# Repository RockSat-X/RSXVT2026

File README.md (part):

# Virginia Tech RockSat-X 2026 Project.

> [!IMPORTANT]
> Quick link to:
> - [Wallops Testing Procedure](#wallops-testing-procedure).
> - [Remove-Before-Flight Procedure](#remove-before-flight-procedure).
>
> Also check out the [RSXVT2026 Wiki](https://github.com/RockSat-X/RSXVT2026/wiki)!

&nbsp;

# Mission Overview.

Our experiment aims to evaluate the use of optical navigation
with Commercial-off-the-Shelf (COTS) products for use in spaceflight applications.
To conduct the experiment,
an autonomous attitude determination and control system (ADCS)
employing an optical navigation system (ONS)
will be designed to control a 1U CubeSat,
codenamed **Commercial Optical Navigation Satellite (CONSat)**.

The 2024 NASA Civil Space Shortfall Ranking lists 9 out of the top 30 shortfalls
as limitations with autonomous deep space navigation.
With recent advancements in computing and ML capabilities,
optical navigation could revolutionize deep space navigation.
Our team aims to address some of the challenges facing the space industry
by designing a cost-effective ADCS that would rely primarily on conditions
only available in deep space.

The CONSat vehicle's Optical Navigation System (ONS) has:
- OpenMV H7+.
- VN-100 IMU / AHRS.

The operating principle of the CONSat will be to:
1. Capture image and isolate target.
2. Perform LoS measurements to estimate attitude.
3. Blend LoS solution with IMU / AHRS solution.
4. Reorient spacecraft to align to target.

The target will be the Earth's horizon as seen at ~190 km apogee.

&nbsp;

# High-Level System Overview.

<p align="center">
<kbd>

<br>
<br>
<em>Deck-plate integrated experiment.</em>
<br>
<br>
</kbd>
</p>&nbsp;

<p align="center">
<kbd>

<br>
<br>
<em>Top-down view of the deck-plate integrated experiment.</em>
<br>
<br>
</kbd>
</p>&nbsp;

<p align="center">
<kbd>

<br>
<br>
<em>Weight of the deck-plate integrated experiment (13.935 pounds / 6.321 kilograms).</em>
<br>
<br>
</kbd>
</p>&nbsp;

<p align="center">
<kbd>

<br>
<br>
<em>Center of gravity of the deck-plate integrated experiment.</em>
<br>
<br>
</kbd>
</p>&nbsp;

<p align="center">
<kbd>

<br>
<br>
<em>The inside of the main electronics box enclosure.</em>
<br>
<br>
</kbd>
</p>&nbsp;

<p align="center">
<kbd>

<br>
<br>
<em>CONSat vehicle.</em>
<br>
<br>
</kbd>
</p>&nbsp;

<p align="center">
<kbd>

<br>
<br>
<em>The inside of the CONSat vehicle.</em>
<br>
<br>
</kbd>
</p>&nbsp;

<p align="center">
<kbd>

<br>
<br>
<em>Labeled CAD model of the experiment.</em>
<br>
<br>
</kbd>
</p>&nbsp;

<p align="center">
<kbd>

<br>
<br>
<em>Functional block diagram of the CONSat experiment.</em>
<br>
<br>
</kbd>
</p>&nbsp;

## Main Camera System.

The experiment has two Main Camera Systems:
one placed before the ejection mechnism
and one next to a Solarboard by the burn-wire mechanism.

<p align="center">
<kbd>

<br>
<br>
<em>Main Camera System demonstration.</em>
<br>
<br>
</kbd>
</p>&nbsp;

The Main Camera System board has a single RGB LED.

| Color          | Description                                                                                          |
| :------------: | ---------------------------------------------------------------------------------------------------- |
| White          | Reformatting uSD card. |
| Magenta        | Initializing uSD card. |
| Blue           | Initializing OV5640 camera module. |
| Toggling green | Recording successfully. |
| Red            | Main Camera System resetting. |

&nbsp;

The Main Camera System creates a binary blob file for each recording.
Use `cli.py parseVideo` to convert the binary blob file into an MP4 video.

&nbsp;

## Debug Board.

The Debug Board has a display to indicate the status of subsystems
from the perspective of the Main Flight Computer.
When the experiment is powered on via GSE-1,
the Debug Board will initialize and play the Nokia buzzer tune.
The display will also periodically invert color;
this is just to indicate that the Debug Board MCU is still running.

<p align="center">
<kbd>

<br>
<br>
<em>Debug board demonstration.</em>
<br>
<br>
</kbd>
</p>&nbsp;

The Debug Board displays the following information.

| Field     | Description                                                                                          |
| :-------: | ---------------------------------------------------------------------------------------------------- |
| `DB-T`    | Time elapsed since the debug board was powered on.                                                   |
| `MFC-T`   | Time elapsed since the Main Flight Compiuter was powered on.                                         |
| `SCB-A`   | Voltage of SB-SCA.                                                                |
| `SCB-B`   | Voltage of HP-SCA.                                                                |
| `te1`     | Whether or not Main Flight Computer is detecting TE-1.                                               |
| `vehicle` | Whether or not Main Flight Computer is communicating with the Vehicle Flight Computer through the vehicle interface. |
| `esp32`   | Whether or not Main Flight Computer is receiving ESP-NOW data packets.                               |
| `lora`    | Whether or not Main Flight Computer is receiving LoRa data packets.                                  |
| `logger`  | Whether or not Main Flight Computer is saving data to its uSD card.                                  |

If the Debug Board has not received the first debug packet from the Main Flight Computer yet,
then the field values will either be `???` or `nan` to indicate this.

> [!IMPORTANT]
> A known issue with the Debug Board's display is that it is not resettable.
> That is, if the Debug Board MCU has a communication issue with the display driver,
> there's a small possibility that the display ends up in a corrupted state.
> This may appear as the screen being darker, the resolution looking off,
> or is completely blank.
> The MCU has no way to fix this,
> but power-cycling will resolve this rare issue if it ever happens.

&nbsp;

The debug board has four RGB LEDs.

| Label     | Position     | Description                                                                                          |
| :-------: | :----------: | ---------------------------------------------------------------------------------------------------- |
| `A`       | Top Right    | Flashes colors when the buzzer is being driven; this is just an extra indicator that's useful for when the buzzer is mute. |
| `B`       | Top Left     | White when the Main Flight Computer hasn't sent the first debug packet to the Debug Board yet; red when there's a bad status to be aware of such as the Main Flight Computer not having received RF data in a while. |
| `C`       | Bottom Right | Toggles red when the Main Flight Computer hasn't sent a debug packet in a while; toggles green when a debug packet has been received. |
| `D`       | Bottom Left  | White when the uSD card is being formatted; magenta when the Debug Board is failing to initialize the uSD card; toggles green periodically when data is successfully being logged to the uSD card. |

> [!IMPORTANT]
> If the Debug Board encounters an irrecoverable error,
> it'll panic and indicate this by flashing all LEDs red.
> The Debug Board should eventually reset itself and continue on as normal.

&nbsp;

The debug board plays the following buzzer tunes.

| Tune                                        | Description                                                                    |
| :---------:                                 | ------------------------------------------------------------------------------ |
| [Nokia      ](./misc/media/nokia.wav      ) | Debug Board is initializing (e.g. just powered on from GSE-1). |
| [Hazard     ](./misc/media/hazard.wav     ) | Debug Board hasn't received a debug packet from the Main Flight Computer in a while. |
| [Up and Down](./misc/media/up_and_down.wav) | `te1` is active (i.e. burn-wire is going). |
| [Deep Beep  ](./misc/media/deep_beep.wav  ) | Main Flight Computer is reporting a bad status (e.g. haven't received RF data in a while) |
| [Tetris     ](./misc/media/tetris.wave    ) | The Debug Board's uSD card is being reformatted. |

To mute the buzzer, leave the header above the buzzer open.
To enable the buzzer, have a jumper shorting two adjacent pins;
which pins are shorted determines the volume of the buzzer.

&nbsp;

The uSD card is optional to the operation of the Debug Board.
The Debug Board uses LED D to indicate that it's successfully saving log data.

<p align="center">
<kbd>

<br>
<br>
<em>
To load a uSD card, lift the connector lid up,
<br>
place the uSD card,
and slide the lid down to secure it.
</em>
<br>
<br>
</kbd>
</p>&nbsp;

<p align="center">
<kbd>

<br>
<br>
<em>
The Debug Board creates an ASCII text file with <br>
the same information displayed on its screen.
</em>
<br>
<br>
</kbd>
</p>&nbsp;

## Vehicle Flight Computer.

The following table details the corresponding buzzer tune and RGB LED behavior for when a Vehicle Flight Computer diagnostic is reported.

| Severity | Tune                                              | RGB LED                 | Description                                                                                          |
|:-:| :-----------------------------------------------: | :-----------------: | ---------------------------------------------------------------------------------------------------- |
| :bangbang:         | [Ambulance  ](./misc/media/ambulance.wav      )   | Fast toggling red   | TMC2209 stepper motor drivers are failing initialization. This could be due to bad ribbon cable connection, dead batteries, inhibited batteries, or something else. |
| :warning:          | [Heartbeat  ](./misc/media/heartbeat.wav      )   | Slow toggling red   | Vehicle Flight Computer has saturated a motor's RPM velocity. |
| :warning:          | [Tetris     ](./misc/media/tetris.wav         )   | Slow toggling white | Vehicle Flight Computer is reformatting the uSD card. |
| :warning:          | [Mario      ](./misc/media/mario.wav          )   | Fast toggling white | Resetting the Vehicle ESP32 due to an issue with it. |
| :warning:          | [Three Tone ](./misc/media/three_tone.wav     )   | Fast toggling white | Resetting the Vehicle OpenMV due to an issue with it. |
| :bangbang:         | [Hazard     ](./misc/media/hazard.wav         )   | Fast toggling blue  | Communication issue with VN-100. |
| :white_check_mark: | [Nokia      ](./misc/media/nokia.wav          )   | Slow toggling white | Vehicle Flight Computer detecting that the vehicle has been redocked. |
| :white_check_mark: | [Birthday   ](./misc/media/birthday.wav       )   | Slow toggling white | Vehicle Flight Computer detecting that the vehicle has been ejected. |
| :warning:          | [Heavy Beep ](./misc/media/heavy_beep.wav     )   | Toggling magenta    | Initialization issue with uSD card. This is okay if no uSD card is loaded. |
| :white_check_mark: | [Burp       ](./misc/media/burp.wav           )   | Blue blink          | VN-100 communication okay. |
| :white_check_mark: | [Chirp      ](./misc/media/chirp.wav          )   | Green blink         | uSD card logging okay. |
| :white_check_mark: | [Waking Up  ](./misc/media/waking_up.wav      )   | None                | Vehicle Flight Computer initializing (i.e. on activation of GSE-1); vehicle batteries are enabled at end of buzzer tune. |
| :white_check_mark: | [Star Wars  ](./misc/media/starwars.wav       )   | None                | Vehicle Flight Computer performing a dock shutdown (i.e. about to turn vehicle batteries off and resetting). |

| Severity            | Description                                                                                          |
| :-----------------: | ---------------------------------------------------------------------------------------------------- |
| :bangbang:  | Something is likely very problematic and should be addressed as soon as possible. |
| :warning:  | A non-fatal or recoverable issue. |
| :white_check_mark:  | Positive or expected indicator of a working system. |

The three pin header on the Vehicle Flight Computer can be left open to mute the buzzer,
otherwise short a pair of adjacent pins to determine the volume of the buzzer.

&nbsp;

The Vehicle Flight Computer board also has an optional uSD card slot for log data.

<p align="center">
<kbd>

<br>
<br>
<em>
The Vehicle Flight Computer creates an ASCII text file with information <br>
like VN-100 IMU data, CVT results, current motor velocities, and so on.
</em>
<br>
<br>
</kbd>
</p>&nbsp;

&nbsp;

## OpenMV H7+.

The OpenMV H7+ has a single RGB LED.

| RGB LED             | Description                                                                                          |
| :-----------------: | ---------------------------------------------------------------------------------------------------- |
| Flashing blue       | The CVT algorithm hasn't detected the horizon yet. |
| Flashing green      | The CVT algorithm has found the horizon. |

Each toggle of the RGB LED represents an entire image being captured, processed, and transmitted to the Vehicle Flight Computer.
Because JPEG image compression is used,
if the OpenMV H7+'s camera lens is covered (e.g. by a finger),
the blinking of the RGB LED will be much faster.

If the OpenMV H7+'s RGB LED is not blinking, then it's very likely the program is not running,
but the Vehicle Flight Computer should reset the OpenMV H7+ eventually after a time-out period.

No other colors or behavior should be expected from the RGB LED or the OpenMV H7+ module as a whole.

&nbsp;

## Vehicle Power Distribution System.

The Vehicle Power Distribution System has LED indicators to be aware of.

| LED                 | Description                                                                                          |
| :-----------------: | ---------------------------------------------------------------------------------------------------- |
| Bright white        | Vehicle interface providing power to the vehicle, thus this LED should be active if and only if the vehicle is docked and GSE-1 is active. |
| Yellow              | Vehicle Flight Computer has enabled on-board battery power. The LED should be off when the Vehicle Flight Computer is initializing but should eventually turn on, unless the vehicle battery inhibit is in place, to which this LED will never turn on. |

The Vehicle Power Distribution System has three jumpers to be aware of.

<p align="center">
<kbd>

<br>
<br>
<em>
First jumper on the left denoted with "M" as in "Motor Inhibit". <br>
Second jumper in the middle denoted with "B" as in "Battery Inhibit". <br>
Third jumper on the right denoted with "P" as in "Power". <br>
Note that the third "Power" jumper should only have its <br>
first left pin and the second right pin is broken off.
</em>
<br>
<br>
</kbd>
</p>&nbsp;

| Jumper              | Activation | Description |
| :-----------------: | - | - |
| "M"                 | Use a shorting 2-pin jumper with pull tab. | Disable the control of the stepper motors. Vehicle Flight Computer can still initialize and operate, but reaction wheels will not spin. This is used to conserve battery charge, if needed. |
| "B"                 | Use a shorting 2-pin jumper with pull tab. | Disable the usage of the vehicle batteries. Vehicle Flight Computer can still initialize and operate via external power through the vehicle interface (i.e. GSE-1), but will immediately unpower upon being undocked. This can also be used to turn off the vehicle manually. |
| "P"                 | Use jumper wire to connect the pin to one of the vehicle batteries' positive terminal and wait several seconds. | Forces the usage of vehicle battery power, thus the Vehicle Flight Computer will initialize. This is to turn the vehicle on without relying on external power. |

> [!TIP]
> A quick way to turn off the vehicle is by using an Allen key to short the middle "B" jumper.

&nbsp;

# RF Verification.

During sequence testing and particularly GPS Roll-Out,
it's critical to verify that RF systems are working as intended
and to communicate this to NASA.

The easiest way to do this is to use the [Debug Board](#debug-board).
The screen will indicate if the Main Flight Computer is receiving RF data from the ESP32 and/or LoRa.
If the Debug Board is loaded with a uSD card,
the RF status will also be logged over time.

A more robust way to verify RF is to use the TinySA Spectrum Analyzer.
There are two particular frequency bands of interest.
| Link  | Center         | Bandwidth      | Start          | End            |
| :---: | :------------: | :------------: | :------------: | :------------: |
| ESP32 | 2.472 GHz      | 20 MHz         | 2.462 GHz      | 2.482 GHz      |
| LoRa  | 920 MHz        | 125 kHz        | 919.9375 MHz   | 920.0625 MHz   |

Configure the spectrum analyzer to observe these frequencies.

<p align="center">
</kbd>
<kbd>

<br>
<br>
<em>
Spectrum analyzer demonstration.
</em>
<br>
<br>
</kbd>
</p>&nbsp;

You should see a reading similar the following figures:

<p align="center">
<kbd>

<br>
<br>
<em>
Spectrum analyzer measurement for the ESP32 link.
</em>
<br>
<br>
</p>
<p align="center">
</kbd>
<kbd>

<br>
<br>
<em>
Spectrum analyzer measurement for the LoRa link.
</em>
<br>
<br>
</kbd>
</p>&nbsp;

> [!IMPORTANT]
> The measurements shown in the figures were taken with an RBW value of 200 Hz;
> this makes the measurement more accurate but at the cost of being extremely slow.
> It's probably more productive to use an auto RBW value so measurements can be done quickly.
> Just as long there is an expected peak within frequency bands, all is good.

The RF verification process and expectations should be roughly as follows:

1. Before the experiment is powered on via GSE-1, no RF transmission is detected within the frequency bands.

2. Shortly after the experiment is powered on via GSE-1,
ESP32 and LoRa transmission can be seen within the frequency bands.

3. RF transmission is sustained for at least the duration of a full mission;
if applicable, the RF transmission should still be sustained even if the vehicle has ejected or becomes undocked.

4. RF transmission is sustained even when main has powered off (i.e. GSE-1 deactived)
as the vehicle will continue transmitting via battery power.

5. RF transmission is no longer detected once the vehicle has powered off
(either by using the vehicle battery inhibit or through a docked reset).

&nbsp;

# Wallops Testing Procedure.

The following table summarizes the primary configurations needed to be set for tests done at Wallops.

| Expected Date                           | Test                         | Allow Ejection?    | Enable TE-1?       | Enable Main GSE-1? | Enable Vehicle GSE-1? |
| :-------------------------------------: | :--------------------------: | :-:                | :-:                | :-:                | :-:                   |
| May 17th, 2026; Sunday                  | Pre-Flight Seq.              | :white_check_mark: | :white_check_mark: | :white_check_mark: | :white_check_mark:    |
| May 18th-19th, 2026; Monday-Tuesday     | Pre-Vibe All-Fire Seq.       | :white_check_mark: | :white_check_mark: | :white_check_mark: | :white_check_mark:    |
| May 18th-19th, 2026; Monday-Tuesday     | Pre-Vibe No-Fire Seq.        | :x:                | :x:                | :white_check_mark: | :white_check_mark:    |
| May 19th, 2026; Tuesday                 | Pre-Vibe Back Up Seq.        | :x:                | :x:                | :white_check_mark: | :white_check_mark:    |
| May 20th-21st, 2026; Wednesday-Thursday | Vibration Testing            | :white_check_mark: | :white_check_mark: | :white_check_mark: | :white_check_mark:    |
| May 22nd, 2026; Friday                  | Post-Vibe All-Fire Seq.      | :white_check_mark: | :white_check_mark: | :white_check_mark: | :white_check_mark:    |
| May 22nd, 2026; Friday                  | Post-Vibe No-Fire Seq.       | :x:                | :x:                | :white_check_mark: | :white_check_mark:    |
| May 22nd, 2026; Friday                  | Post-Vibe Back Up Seq.       | :x:                | :x:                | :white_check_mark: | :white_check_mark:    |
| May 22nd, 2026; Friday                  | GPS Roll-Out                 | :x:                | :x:                | :white_check_mark: | :white_check_mark:    |
| June 19th, 2026; Friday                 | Final All-Fire Seq.          | :white_check_mark: | :white_check_mark: | :white_check_mark: | :white_check_mark:    |
| June 19th, 2026; Friday                 | Final No-Fire Seq.           | :x:                | :x:                | :white_check_mark: | :white_check_mark:    |
| June 19th, 2026; Friday                 | Final Back Up Seq.           | :x:                | :x:                | :white_check_mark: | :white_check_mark:    |

To allow ejection ( :white_check_mark: ),
ensure the mechanical inhibit in front of the ejection mechanism is removed.

To prevent ejection ( :x: ),
ensure the mechanical inhibit is secured in front of the ejection mechanism.

To have TE-1, Main GSE-1, or Vehicle GSE-1 be enabled ( :white_check_mark: ),
insert a screw into the corresponding electrical screw switch on the side of the ejection mechanism.
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
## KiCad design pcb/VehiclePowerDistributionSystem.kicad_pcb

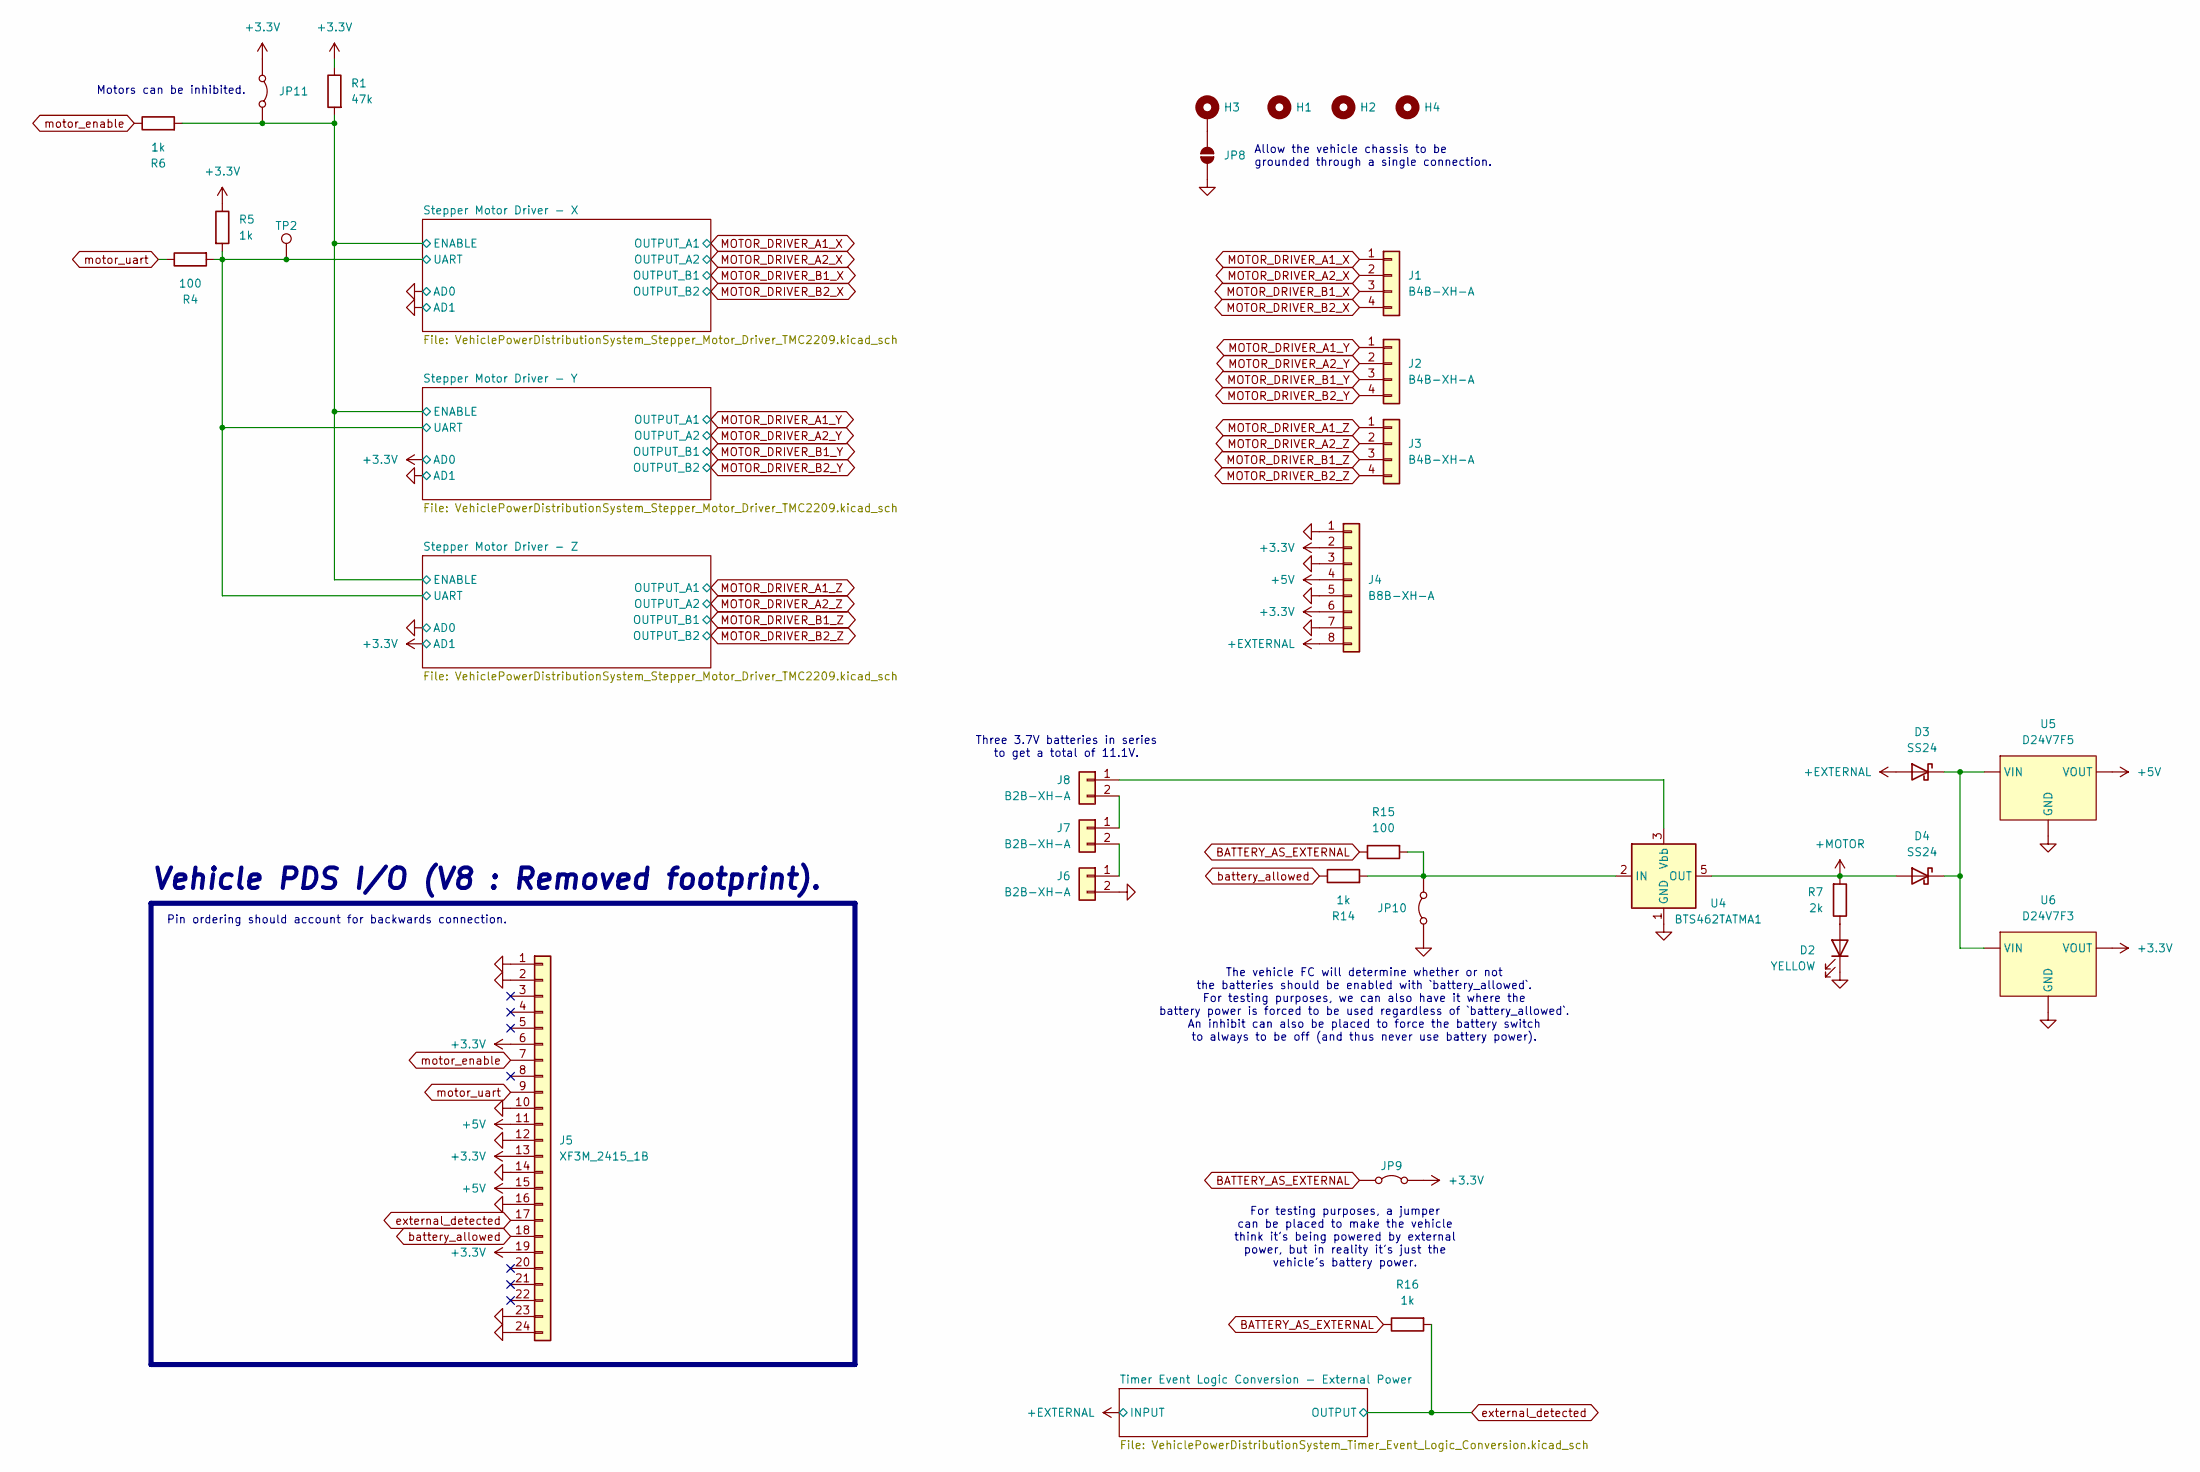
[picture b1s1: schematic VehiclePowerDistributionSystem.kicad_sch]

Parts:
D2: YELLOW; LED_1206_3216Metric_Pad1.42x1.75mm_HandSolder
D3, D4: SS24; D_SMA-SMB_Universal_Handsoldering
H1, H2, H4: MountingHole; MountingHole_3.2mm_M3
H3: MountingHole_Pad; MountingHole_3.2mm_M3_DIN965_Pad
J1, J2, J3: B4B-XH-A; JST_XH_B4B-XH-A_1x04_P2.50mm_Vertical
J4: B8B-XH-A; JST_XH_B8B-XH-A_1x08_P2.50mm_Vertical
J5: XF3M_2415_1B; XF3M_2415_1B - REVERSED
J6, J7, J8: B2B-XH-A; JST_XH_B2B-XH-A_1x02_P2.50mm_Vertical
JP8: SolderJumper_2_Open; SolderJumper-2_P1.3mm_Open_RoundedPad1.0x1.5mm
JP9, JP10, JP11: Jumper_2_Bridged; NPC02SXON-RC
R1: 47k; R_1206_3216Metric_Pad1.30x1.75mm_HandSolder
R4, R15: 100; R_1206_3216Metric_Pad1.30x1.75mm_HandSolder
R5, R6, R14, R16: 1k; R_1206_3216Metric_Pad1.30x1.75mm_HandSolder
R7: 2k; R_1206_3216Metric_Pad1.30x1.75mm_HandSolder
TP2: TestPoint; TestPoint_Bridge_Pitch2.0mm_Drill0.7mm
U4: BTS462TATMA1; TO-252-4
U5: D24V7F5; D24V7Fx
U6: D24V7F3; D24V7Fx

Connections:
+3.3V: J4.2, J4.6, J5.6, J5.13, J5.19, JP9.1 (A), JP11.1 (A), R1.1, R5.1, U6.VOUT; also elsewhere on the board
+5V: J4.4, J5.11, J5.15, U5.VOUT
+EXTERNAL: D3.2 (A), J4.8; also elsewhere on the board
+MOTOR: D4.2 (A), R7.2, U4.5 (OUT); also elsewhere on the board
/Stepper Motor Driver - X/ENABLE: JP11.2 (B), R1.2, R6.2; also elsewhere on the board
/Stepper Motor Driver - X/UART: R4.2, R5.2, TP2.1; also elsewhere on the board
BATTERY_AS_EXTERNAL: JP9.2 (B), R15.1, R16.1
GND: D2.1 (K), J4.1, J4.3, J4.5, J4.7, J5.1, J5.2, J5.10, J5.12, J5.14, J5.16, J5.23, J5.24, J6.2, JP8.1 (A), JP10.1 (A), U4.1 (GND), U5.GND, U6.GND; also elsewhere on the board
MOTOR_DRIVER_A1_X: J1.1; also elsewhere on the board
MOTOR_DRIVER_A1_Y: J2.1; also elsewhere on the board
MOTOR_DRIVER_A1_Z: J3.1; also elsewhere on the board
MOTOR_DRIVER_A2_X: J1.2; also elsewhere on the board
MOTOR_DRIVER_A2_Y: J2.2; also elsewhere on the board
MOTOR_DRIVER_A2_Z: J3.2; also elsewhere on the board
MOTOR_DRIVER_B1_X: J1.3; also elsewhere on the board
MOTOR_DRIVER_B1_Y: J2.3; also elsewhere on the board
MOTOR_DRIVER_B1_Z: J3.3; also elsewhere on the board
MOTOR_DRIVER_B2_X: J1.4; also elsewhere on the board
MOTOR_DRIVER_B2_Y: J2.4; also elsewhere on the board
MOTOR_DRIVER_B2_Z: J3.4; also elsewhere on the board
unnamed: D2.2 (A), R7.1
unnamed: D3.1 (K), D4.1 (K), U5.VIN, U6.VIN
unnamed: J6.1, J7.2
unnamed: J7.1, J8.2
unnamed: J8.1, U4.3 (Vbb)
unnamed: H3.1, JP8.2 (B)
unnamed: JP10.2 (B), R14.2, R15.2, U4.2 (IN)
battery_allowed: J5.18, R14.1
external_detected: J5.17, R16.2; also elsewhere on the board
motor_enable: J5.7, R6.1
motor_uart: J5.9, R4.1

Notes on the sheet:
Pin ordering should account for backwards connection.
Three 3.7V batteries in series to get a total of 11.1V.
Allow the vehicle chassis to be grounded through a single connection.
For testing purposes, a jumper can be placed to make the vehicle think it's being powered by external power, but in reality it's just the vehicle's battery power.
Vehicle PDS I/O (V8 : Removed footprint).
The vehicle FC will determine whether or not the batteries should be enabled with `battery_allowed`. For testing purposes, we can also have it where the battery power is forced to be used regardless of `battery_allowed`. An inhibit can also be placed to force the battery switch to always to be off 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
Motors can be inhibited.

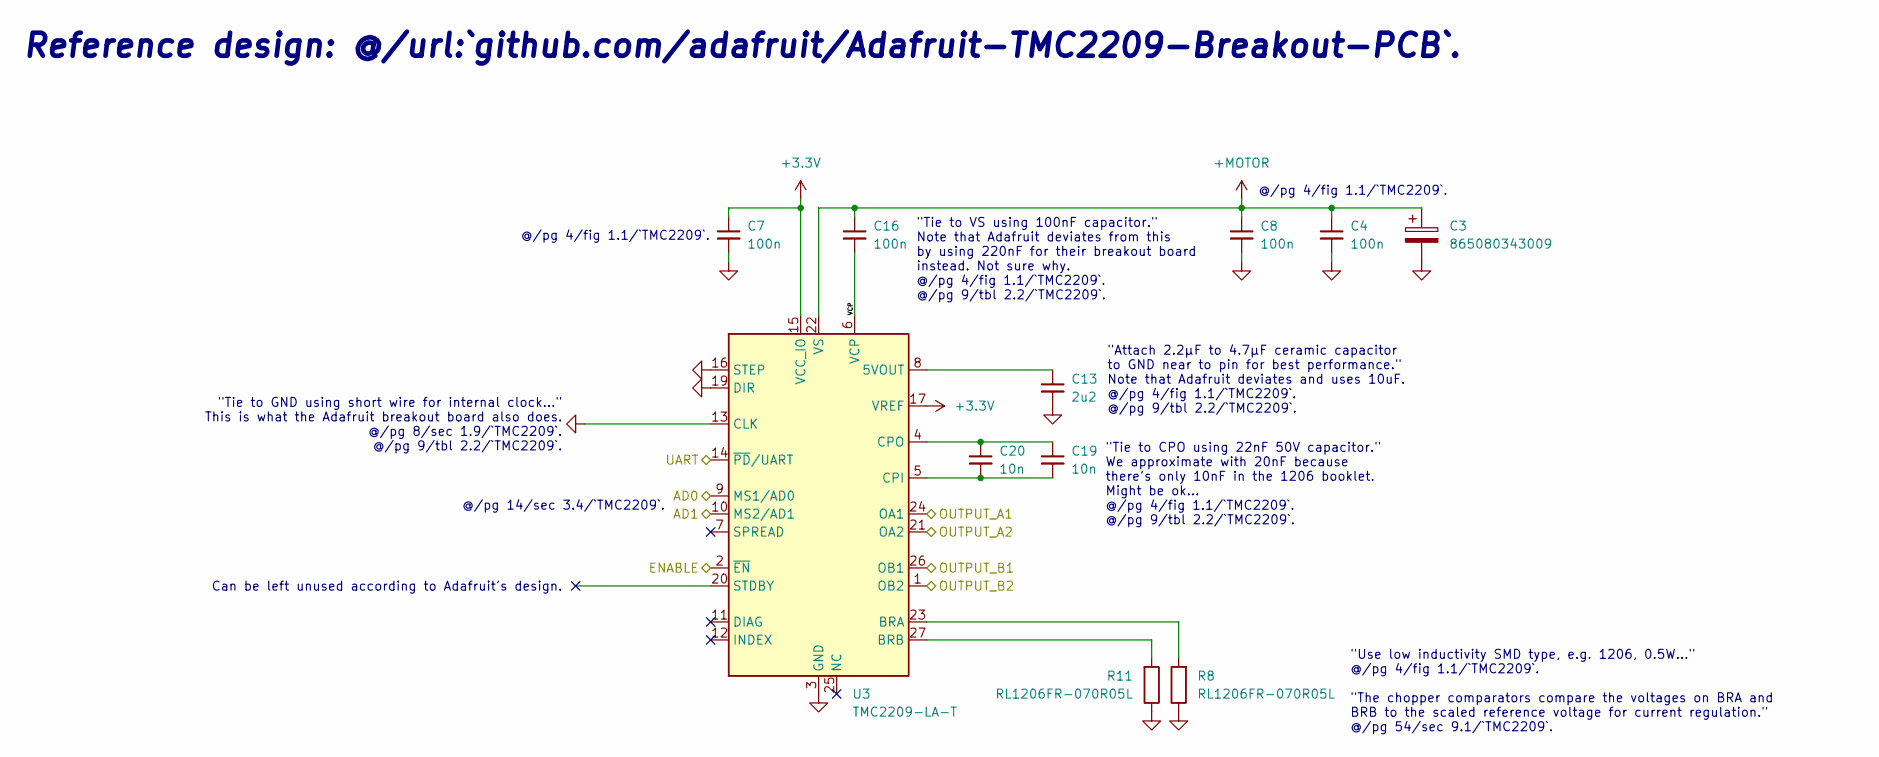
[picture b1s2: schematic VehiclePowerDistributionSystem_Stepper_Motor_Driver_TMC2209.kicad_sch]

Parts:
C3: 865080343009; CP_Elec_6.3x5.4
C4, C7, C8, C16: 100n; C_1206_3216Metric_Pad1.33x1.80mm_HandSolder
C13: 2u2; C_1206_3216Metric_Pad1.33x1.80mm_HandSolder
C19, C20: 10n; C_1206_3216Metric_Pad1.33x1.80mm_HandSolder
R8, R11: RL1206FR-070R05L; R_1206_3216Metric_Pad1.30x1.75mm_HandSolder
U3: TMC2209-LA-T; VQFN-28-1EP_5x5mm_P0.5mm_EP3.7x3.7mm_ThermalVias

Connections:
+3.3V: C7.1, U3.10 (MS2/AD1), U3.15 (VCC_IO), U3.17 (VREF); also elsewhere on the board
+MOTOR: C3.1, C4.1, C8.1, C16.1, U3.22 (VS), U3.28 (VS); also elsewhere on the board
/Stepper Motor Driver - X/ENABLE: U3.2 (~EN); also elsewhere on the board
/Stepper Motor Driver - X/UART: U3.14 (~PD/UART); also elsewhere on the board
/Stepper Motor Driver - Z/VCP: C16.2, U3.6 (VCP)
GND: C3.2, C4.2, C7.2, C8.2, C13.2, R8.1, R11.1, U3.3 (GND), U3.9 (MS1/AD0), U3.13 (CLK), U3.16 (STEP), U3.18 (GND), U3.19 (DIR), U3.29 (GND); also elsewhere on the board
MOTOR_DRIVER_A1_Z: U3.24 (OA1); also elsewhere on the board
MOTOR_DRIVER_A2_Z: U3.21 (OA2); also elsewhere on the board
MOTOR_DRIVER_B1_Z: U3.26 (OB1); also elsewhere on the board
MOTOR_DRIVER_B2_Z: U3.1 (OB2); also elsewhere on the board
unnamed: C13.1, U3.8 (5VOUT)
unnamed: R8.2, U3.23 (BRA)
unnamed: R11.2, U3.27 (BRB)
unnamed: C19.2, C20.2, U3.5 (CPI)
unnamed: C19.1, C20.1, U3.4 (CPO)

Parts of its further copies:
C1, C2: 865080343009; CP_Elec_6.3x5.4
C5, C6, C9, C10, C11, C12, C17, C18: 100n; C_1206_3216Metric_Pad1.33x1.80mm_HandSolder
C14, C15: 2u2; C_1206_3216Metric_Pad1.33x1.80mm_HandSolder
C21, C22, C23, C24: 10n; C_1206_3216Metric_Pad1.33x1.80mm_HandSolder
R9, R10, R12, R13: RL1206FR-070R05L; R_1206_3216Metric_Pad1.30x1.75mm_HandSolder
U1, U2: TMC2209-LA-T; VQFN-28-1EP_5x5mm_P0.5mm_EP3.7x3.7mm_ThermalVias

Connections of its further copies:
+3.3V: C9.1, C11.1, U1.15 (VCC_IO), U1.17 (VREF), U2.9 (MS1/AD0), U2.15 (VCC_IO), U2.17 (VREF); also elsewhere on the board
+MOTOR: C1.1, C2.1, C5.1, C6.1, C10.1, C12.1, C17.1, C18.1, U1.22 (VS), U1.28 (VS), U2.22 (VS), U2.28 (VS); also elsewhere on the board
/Stepper Motor Driver - X/ENABLE: U1.2 (~EN), U2.2 (~EN); also elsewhere on the board
/Stepper Motor Driver - X/UART: U1.14 (~PD/UART), U2.14 (~PD/UART); also elsewhere on the board
/Stepper Motor Driver - X/VCP: C18.2, U1.6 (VCP)
/Stepper Motor Driver - Y/VCP: C17.2, U2.6 (VCP)
GND: C1.2, C2.2, C5.2, C6.2, C9.2, C10.2, C11.2, C12.2, C14.2, C15.2, R9.1, R10.1, R12.1, R13.1, U1.3 (GND), U1.9 (MS1/AD0), U1.10 (MS2/AD1), U1.13 (CLK), U1.16 (STEP), U1.18 (GND), U1.19 (DIR), U1.29 (GND), U2.3 (GND), U2.10 (MS2/AD1), U2.13 (CLK), U2.16 (STEP), U2.18 (GND), U2.19 (DIR), U2.29 (GND); also elsewhere on the board
MOTOR_DRIVER_A1_X: U1.24 (OA1); also elsewhere on the board
MOTOR_DRIVER_A1_Y: U2.24 (OA1); also elsewhere on the board
MOTOR_DRIVER_A2_X: U1.21 (OA2); also elsewhere on the board
MOTOR_DRIVER_A2_Y: U2.21 (OA2); also elsewhere on the board
MOTOR_DRIVER_B1_X: U1.26 (OB1); also elsewhere on the board
MOTOR_DRIVER_B1_Y: U2.26 (OB1); also elsewhere on the board
MOTOR_DRIVER_B2_X: U1.1 (OB2); also elsewhere on the board
MOTOR_DRIVER_B2_Y: U2.1 (OB2); also elsewhere on the board
unnamed: C15.1, U1.8 (5VOUT)
unnamed: R10.2, U1.23 (BRA)
unnamed: R13.2, U1.27 (BRB)
unnamed: C23.2, C24.2, U1.5 (CPI)
unnamed: C23.1, C24.1, U1.4 (CPO)
unnamed: C14.1, U2.8 (5VOUT)
unnamed: R9.2, U2.23 (BRA)
unnamed: R12.2, U2.27 (BRB)
unnamed: C21.2, C22.2, U2.5 (CPI)
unnamed: C21.1, C22.1, U2.4 (CPO)

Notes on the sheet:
"Tie to CPO using 22nF 50V capacitor." We approximate with 20nF because there's only 10nF in the 1206 booklet. Might be ok... @/pg 4/fig 1.1/`TMC2209`. @/pg 9/tbl 2.2/`TMC2209`.
Reference design: @/url:`github.com/adafruit/Adafruit-TMC2209-Breakout-PCB`.
@/pg 4/fig 1.1/`TMC2209`.
Can be left unused according to Adafruit's design.
@/pg 14/sec 3.4/`TMC2209`.
"Tie to GND using short wire for internal clock..." This is what the Adafruit breakout board also does. @/pg 8/sec 1.9/`TMC2209`. @/pg 9/tbl 2.2/`TMC2209`.
"Use low inductivity SMD type, e.g. 1206, 0.5W..." @/pg 4/fig 1.1/`TMC2209`. "The chopper comparators compare the voltages on BRA and BRB to the scaled reference voltage for current regulation." @/pg 54/sec 9.1/`TMC2209`.
"Tie to VS using 100nF capacitor." Note that Adafruit deviates from this by using 220nF for their breakout board instead. Not sure why. @/pg 4/fig 1.1/`TMC2209`. @/pg 9/tbl 2.2/`TMC2209`.
"Attach 2.2μF to 4.7μF ceramic capacitor to GND near to pin for best performance." Note that Adafruit deviates and uses 10uF. @/pg 4/fig 1.1/`TMC2209`. @/pg 9/tbl 2.2/`TMC2209`.

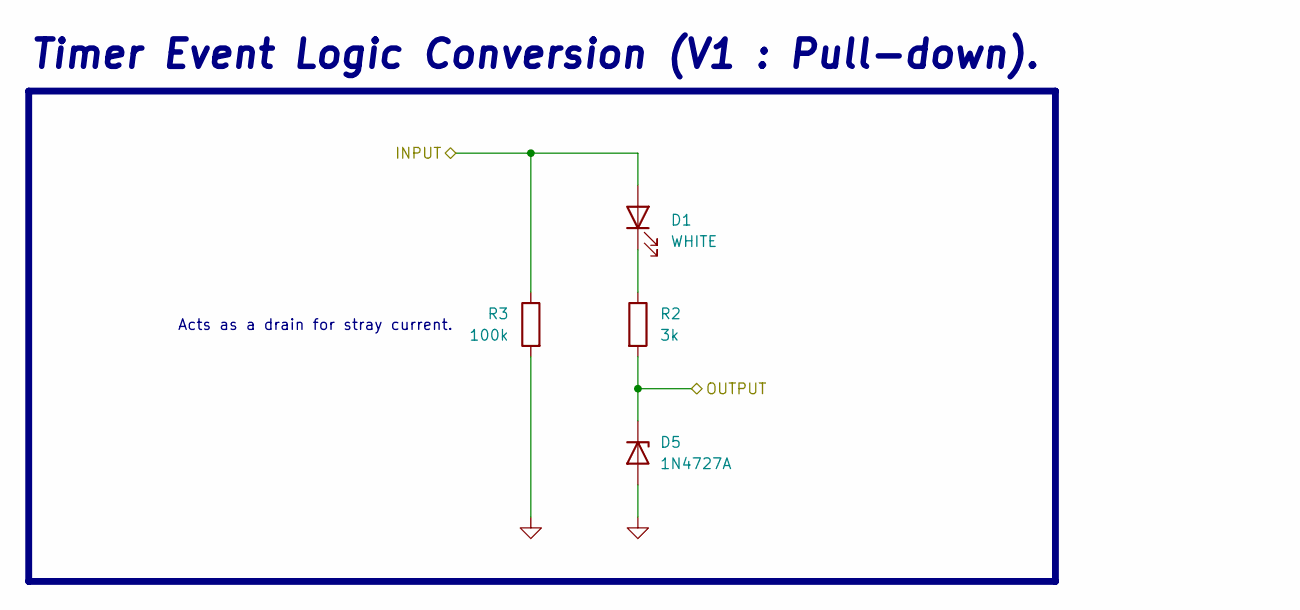
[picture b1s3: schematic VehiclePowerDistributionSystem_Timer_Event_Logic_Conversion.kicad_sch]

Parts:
D1: WHITE; LED_1206_3216Metric_Pad1.42x1.75mm_HandSolder
D5: 1N4727A; D_A-405_P7.62mm_Horizontal
R2: 3k; R_1206_3216Metric_Pad1.30x1.75mm_HandSolder
R3: 100k; R_1206_3216Metric_Pad1.30x1.75mm_HandSolder

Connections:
+EXTERNAL: D1.2 (A), R3.1; also elsewhere on the board
GND: D5.2 (A), R3.2; also elsewhere on the board
unnamed: D1.1 (K), R2.1
external_detected: D5.1 (K), R2.2; also elsewhere on the board

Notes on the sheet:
Timer Event Logic Conversion (V1 : Pull-down).
Acts as a drain for stray current.

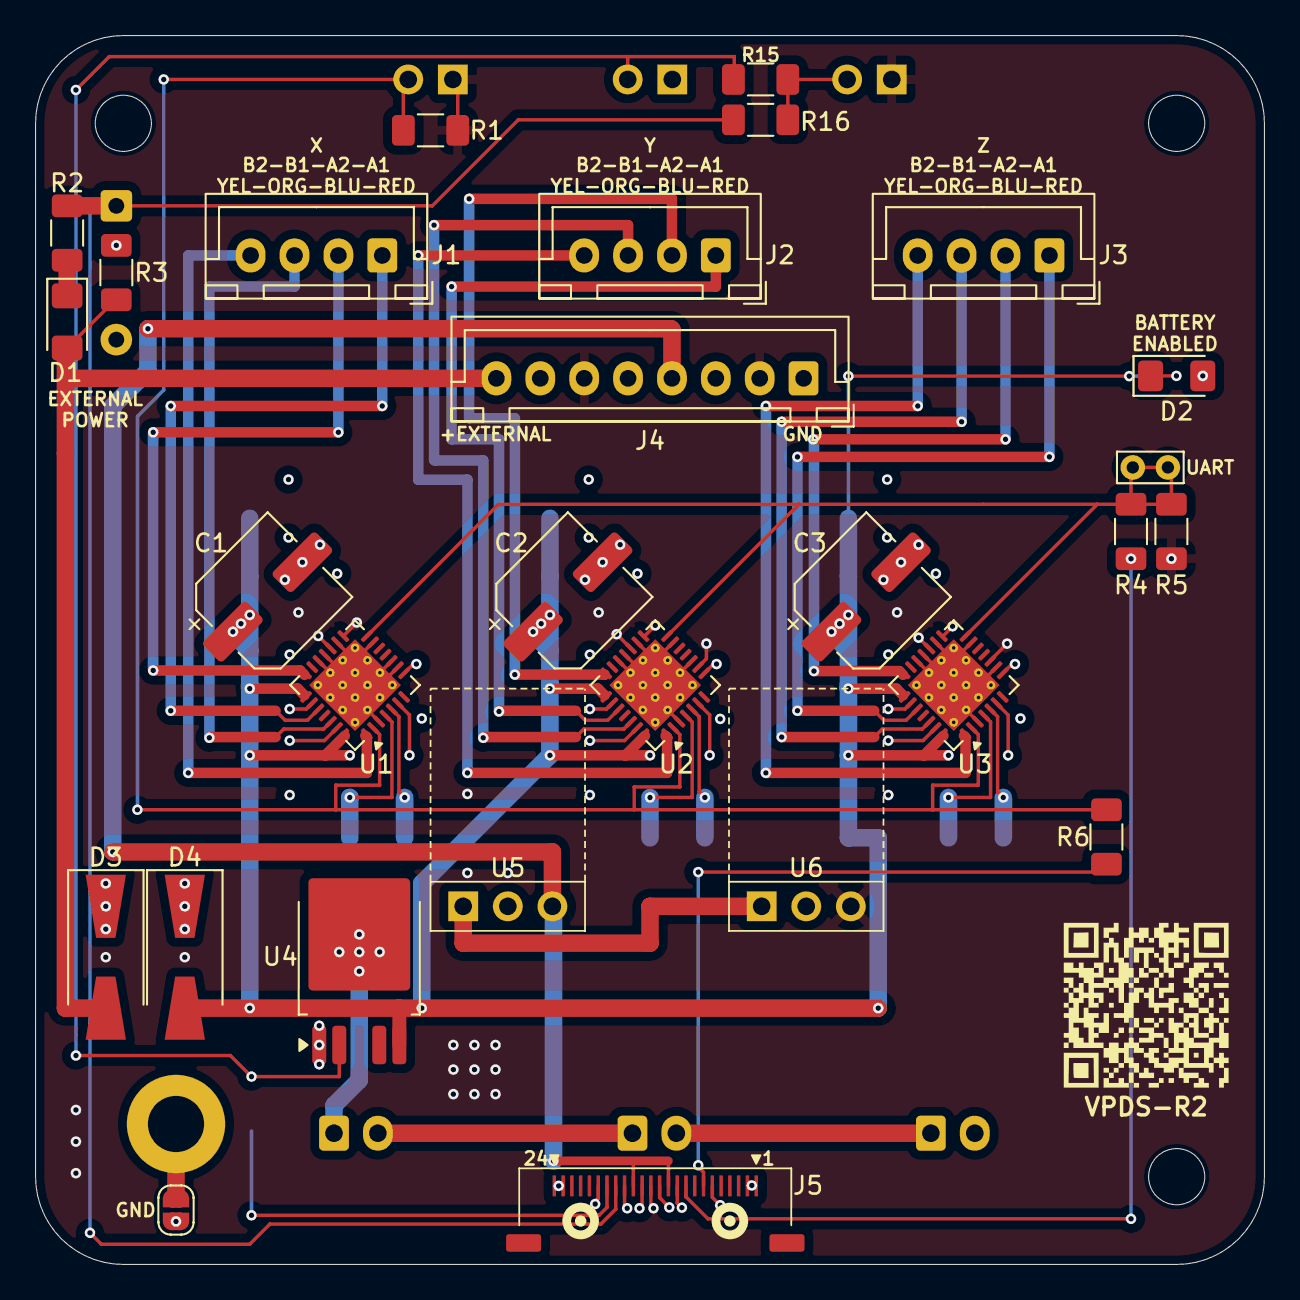
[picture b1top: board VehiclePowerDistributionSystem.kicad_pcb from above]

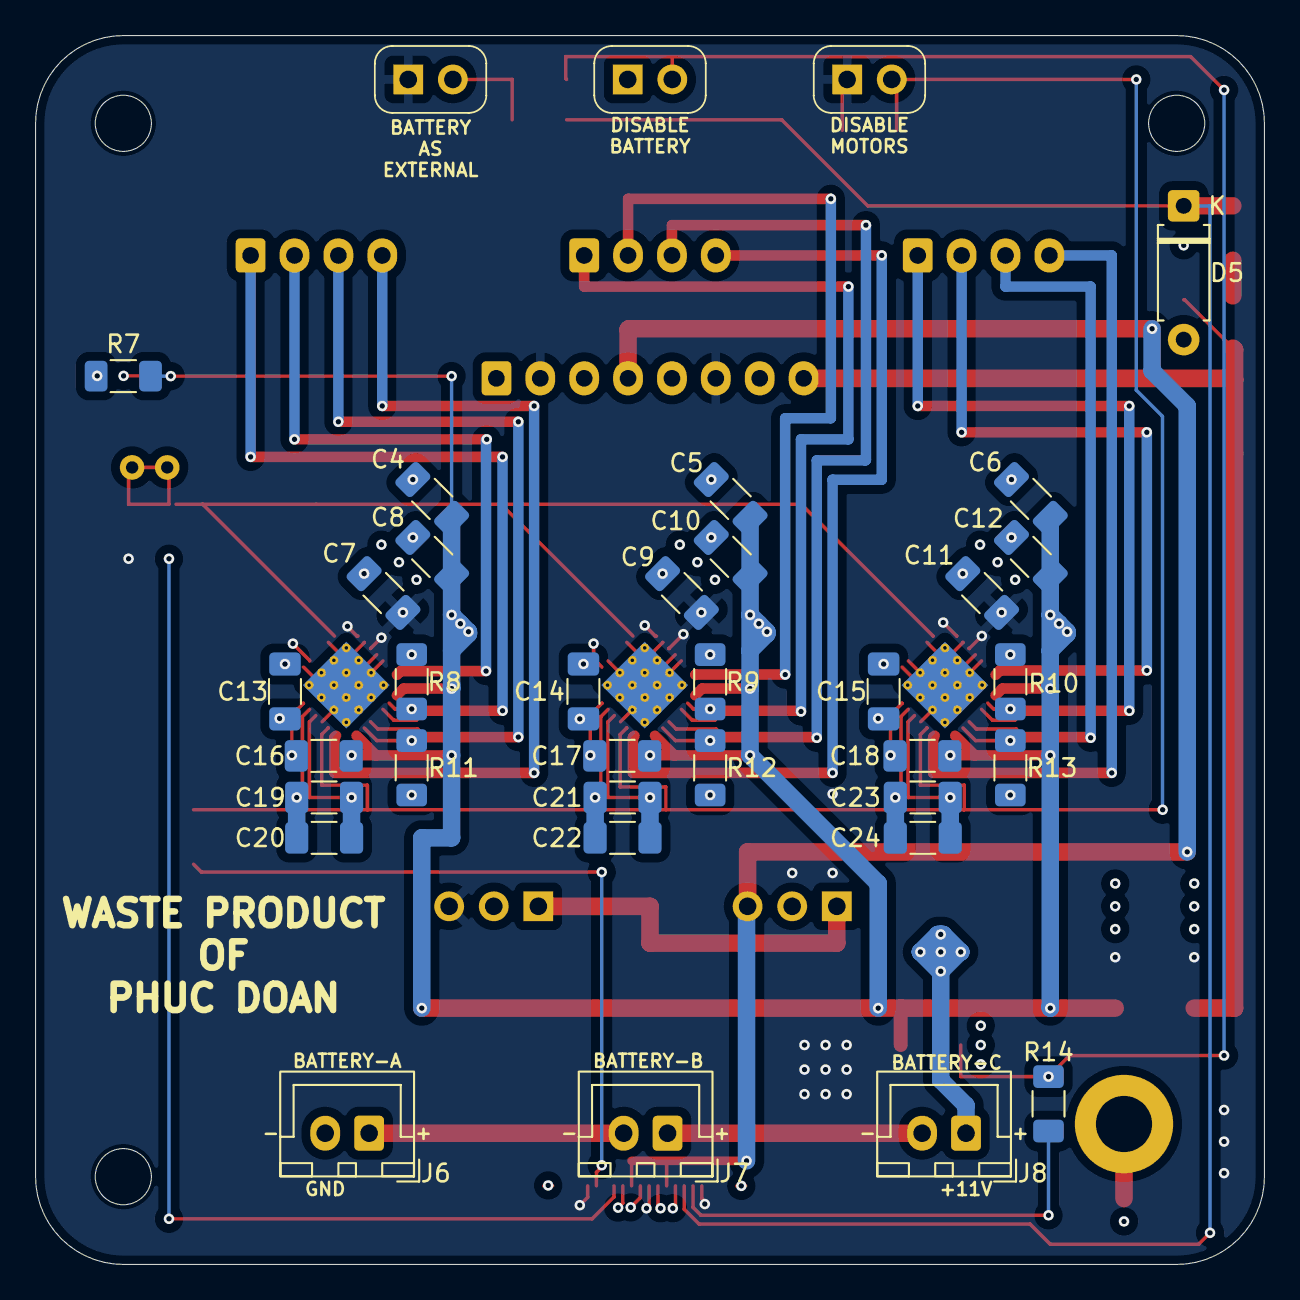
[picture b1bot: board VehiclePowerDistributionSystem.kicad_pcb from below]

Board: 4 copper layers, 70.0 x 70.0 mm, 69 parts (36 on the bottom side), 50 nets.

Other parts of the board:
N1: Housing; Dummy

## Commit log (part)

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2026-03-08 Have `magnetic_disturbance_exists` and `acceleration_disturbance_exists` be logged.
2026-03-09 Setting up `openmv` task.
2026-03-09 `SPIBlock` can now also be indexed in units of 32-bit words; added additional bug assertions.
2026-03-09 Putting OpenMV packets into ring-buffers.
2026-03-09 Fixed broken `DemoSPI`.
2026-03-09 Having OpenMV transmit GNC and image packets.
2026-03-09 Resetting the OpenMV with `openmv_reset`.
2026-03-10 Having the user parameterize the SPI ring-buffer length.
2026-03-10 SPI driver now only supports the SPI2 peripheral.
2026-03-10 Have SPI driver use DMA for reception.
2026-03-10 Having `struct.pack` be done in little-endian to remove padding.
2026-03-10 Collecting OpenMV image data in a much more structured way.
2026-03-10 Cleaned up the `openmv` task.
2026-03-10 python script and output mp4
2026-03-11 Inlined `diagnostics_delay_ms`.
2026-03-11 Resetting OpenMV on time-out.
2026-03-11 Removed `Log file index` metric from logs.
2026-03-11 Added OpenMV GNC data to logs; using entire `working_sectors` to make log entries.
2026-03-11 Using `vel_rw.txt` for the mock `SEQUENCE_ANGULAR_ACCELERATIONS`.
2026-03-11 Added `ESPNOW_ENABLE` and `LORA_ENABLE` switches.
2026-03-11 Renamed `PacketESP32` and `PacketLoRa` to `ESP32Packet` and `LoRaPacket` respectively for consistency.
2026-03-11 `GENERATE_DUMMY_PACKETS` no longer fills in the sequence number of the payload.
2026-03-11 Redefined some `struct LoRaPacket` and `struct ESP32Packet` members.
2026-03-11 Setting up `MainFlightComputer_NUCLEO` to display received ESP32 data.
2026-03-11 Increased OpenMV resolution to `SIF`.
2026-03-12 Resetting the ESP32 on reset.
2026-03-12 Incrementing `esp32_issues` on each error.
2026-03-12 Typo.
2026-03-12 Have less ambiguous enumeration member names for `I2CSlaveCallbackEvent`.
2026-03-12 Cleaned up `INTERRUPT_I2Cx_vehicle_interface` a bit.
2026-03-12 Adjusted buzzer tune and delay for the `watchdog` task.
2026-03-12 Vehicle resetting when it detects it is still docked and that main is likely not powered.
2026-03-12 Slimmed down `MainFlightComputer`.
2026-03-12 Handling ESP32 timeouts with resets.
2026-03-13 Bare-minimum to set up vehicle interface communication for `MainFlightComputer`.
2026-03-13 A docked reset is done when the vehicle interface I2C bus is held down for long enough.
2026-03-13 Setting up `logger` task for `MainFlightComputer`.
2026-03-13 gnc drivers development
2026-03-13 Fixed case-sensitivity of file path inclusion of `./deps/CMSIS-DSP/Include`.
2026-03-13 Ensuring `struct OpenMVPacketGNC` and `struct OpenMVPacketImage` are the same size.
2026-03-14 Reimplemented matrix stuff.
2026-03-14 Split `GNCParameters` into `GNCInput` and `GNCContext`.
2026-03-14 Implemented `stlink_tx_GNCContext`.
2026-03-14 Outputting row number instead of entry index.
2026-03-14 Reintroduced `PI` constant to fix compilation of `stepper.c`.
2026-03-15 Added another case of `SDCmderIterateResult_card_glitch`.
2026-03-15 Added she-bang; using command-line arguments to provide input file path.
2026-03-15 Cleaned up `INTERRUPT_I2Cx_communication`.
2026-03-17 Parsing main camera system's log file one chunk at a time instead of loading entire file into memory.
2026-03-17 Using `-O3` when target is flight-ready.
2026-03-17 Playing buzzer tune for when a packet from the debugged-device hasn't been received in a while.
2026-03-17 Inlined `current_timestamp_us`.
2026-03-17 Removed stale scripts and reorganized.
2026-03-17 Replaced usage of `.format` with f-strings.
2026-03-17 Scaling the sample images on the SD card to fit the sensor's framebuffer.
2026-03-17 Added a case `FileSystemReinitResult_no_more_space_for_new_file` using `f_getfree`.
2026-03-17 Starting to clean up sample frame processing.
2026-03-17 Beginning to refactor with `process_sample_frame`.
2026-03-18 `process_sample_frame` takes `sample_frame_file_path` argument instead.
2026-03-18 Inlined `draw_fitted_curve`.
2026-03-22 Inlined `is_plausible_horizon`.
2026-03-22 Inlined `find_gradient_points`.
2026-03-23 Removed `skip_frames`.
2026-03-23 Starting to generalize with `find_peak_delta`.
2026-03-24 Displaying colored framebuffer now.
2026-03-24 Removed need for `step` of `find_peak_delta`.
2026-03-24 Turned `find_peak_delta` into `scan_peak_delta`.
2026-03-24 Shortened narrow scan stage.
2026-03-24 Merged `OpenMV.py` and `OpenMV_CurveFitting.py`.
2026-03-24 Minor adjustments.
2026-03-24 Changed reported SolarBoard voltages to be `f32`.
2026-03-24 Revert "Having `SandboxNucleoBoard` mock communication with `DebugBoard`."
    This reverts commit b50777d57b0e7938c251f4c1feccffce526cbe7f.
    # Conflicts:
    # electrical/SandboxNucleoBoard.c
2026-03-24 LED blinks on each log entry written.
2026-03-25 Removed `live_for_too_long` reset condition.
2026-03-25 Removed some to-dos.
2026-03-27 Initial commit: New esp_now and LoRa init functions and reset timers
2026-03-29 Using LED C to indicate `havent_received_a_packet_in_a_while` condition.
2026-03-29 Removed the mock of VN-100 from `MainFlightComputer`.
2026-03-29 Added `FileSystemDiskInitializeImplementationResult_initer_timeout` error condition.
2026-03-29 Dynamic time-out duration for `esp32_get_byte`.
2026-03-30 Inducing an ESP32 reset when encountering too many consecutive CRC errors for `MainFlightComputer`.
2026-03-30 Cleaned up `vehicle_interface` task for `MainFlightComputer`.
2026-03-30 Sending some log entries over ST-Link for `MainFlightComputer`.
2026-03-31 update to esp/lora init
2026-03-31 Buffering up multiple `struct LogEntry`s before writing them to the SD card for `MainFlightComputer`.
2026-03-31 Making a log entry only if data exists for `MainFlightComputer`.
2026-03-31 Sending ESP32 and LoRa status from `MainFlightComputer` to `DebugBoard`.
2026-04-01 implemented GNC algo
    not finished yet
2026-04-01 Removed the usage of `print` in `process_framebuffer`.
2026-04-01 Inlined `get_attitude`.
2026-04-01 Changed `sensor.get_fb()` to `working_framebuffer` when getting center of the working framebuffer.
2026-04-01 updated algorithm
    used trig (slang for trigonometry) to find the closest point
    also added more pictures
2026-04-02 Rolled back bad changes.
2026-04-03 Cleaned up `parseVideo`.
2026-04-03 Invoking `ffmpeg` to compress the generated video of `parseVideo`.
2026-04-03 Fixed edge case of logging results when `ffmpeg` is not found.
2026-04-03 Using `Gyan.FFmpeg` instead of `Gyan.FFmpeg.Full`.
2026-04-03 Defining `struct LoRaPacket`, `struct ESP32Packet`, `struct VehicleInterfacePayload`, and `struct MainFlightComputerLogEntry` with a meta-directive.
2026-04-03 `parseFlight` taking in `output_directory_path` argument.
2026-04-03 Conditionally outputting a cell value in the CSV if the packet exists for it.
2026-04-04 refined gnc guidance algorithm
    implemented sinusoidal search pattern.
    need to finish gain selection and implement buffer
2026-04-04 Deprecated `GNCContext.meta`; defining `struct GNCContext` explicitly.
2026-04-04 Inlined `gain_matrix_select`.
2026-04-04 Made `operation_mode` into an enumeration.
2026-04-04 Simplified usage of the `state` variable.
2026-04-04 Implemented `MATRIX_scale_add`.
2026-04-04 Setting up state machine for GNC.
2026-04-04 Cleaned up and commented state machine behavior.
2026-04-04 Cleaned up and reorganized sections within `GNC_update`.
2026-04-04 Cleaned up computation of errors.
2026-04-04 Initializing `struct GNCContext` thoroughly.
2026-04-04 Visualizing orientation of VN-100 quaternion.
2026-04-05 Visualizing the angular velocities of the axes.
2026-04-05 `VehicleFlightComputer` slowing down transmission to vehicle ESP32 when ESP-NOW ring-buffer approaches being full; adjusted task priorities to prioritize ESP32 transmission.
2026-04-05 Having `DemoGNC` send `PlotSnapshot`s to be later plotted.
2026-04-06 Removed need for named-tuple `VN100Register`.
2026-04-06 Refined Init and helper functions, established TX/RX error functions
2026-04-06 Button to load a snapshot file.
2026-04-06 `plot` taking `input_file_path`.
2026-04-06 Using `Button` for `stlink_button`.
2026-04-07 Having keybindings for `plot`.
2026-04-07 Using `timestamp_us` field from snapshots to infer the reference time.
2026-04-07 Better visualization for rotational arrows at varying angular velocities.
2026-04-07 Keybinding for toggling full-screen.
2026-04-07 Reduced default size of window.
2026-04-07 Having a time-out when waiting for data from the ST-Link.
2026-04-07 Plotting the angular velocities over time.
2026-04-07 More interesting angular accelerations for `DemoGNC`.
2026-04-07 Plotting angular accelerations.
2026-04-07 Having timeline slider stretch the entire width of the window.
2026-04-07 Handling timestamp overflow better.
2026-04-08 Checking for existence of input file path for `parseFlight`.
2026-04-08 `parseFlight` processing the image data to make a video.
2026-04-08 Making `VideoMaker` to simplify the process of making videos from image frames.
2026-04-08 Making `parseVideo` use `VideoMaker`.
2026-04-09 Having generated structures be aliased to `struct Sector` if applicable.
2026-04-09 Having `pack_push` and `pack_pop` in `PacketStructures.meta`.
2026-04-09 Fixed ESP32 Arduino compilation.
2026-04-13 Reintroduced buzzer into `MainFlightComputer`.
2026-04-18 added TX/RX error detection
2026-04-20 fixed packet transmission pause and blocking errors
2026-04-20 Fixed issues
2026-04-20 Fixed annotation bug; using `QQVGA` resolution.
2026-04-20 (Missing Meta) Detecting when the vehicle has ejected or been redocked.
2026-04-20 Adjusted some more settings for `MainCameraSystem`.
2026-04-20 `MainFlightComputer` flashing LED to indicate life.
2026-04-22 `stpy`: "Patched missing register setting for ADC configuration."
2026-04-22 `MainFlightComputer` always periodically logging data for Solarboards.
2026-04-22 Defining `PI` only when needed.
2026-04-22 Current draw measurement.
2026-04-22 Iterating through all status flags instead of the amount based on the display.
2026-04-22 Added `timer_event_1` to `MainFlightComputerLogEntry`.
2026-04-22 Relaxed the status check for ESP32 on `MainFlightComputer`.
2026-04-23 finalized cvt attiude estimates
    correct error implementation
2026-04-27 Adjusting the frequency band of LoRa per FMSR action item.
2026-04-28 Adjusting the RF settings per Wesley's update.
2026-04-28 Marked `spi.c` as production-ready.
2026-04-28 Setting up sections and media of `README.md`.
2026-04-29 Beginning to document debug board.
2026-04-29 Completed: Added more details to debug board.
2026-04-29 Added note about the debug board panicking.
2026-04-29 Added section for Main Camera System.
2026-04-30 Began section for Wallops Testing Procedure.
2026-04-30 Filled out the procedure for performing a battery swap.
2026-05-01 Adjusted attitude calculation.
2026-05-01 Revert "Adjusted attitude calculation."
    This reverts commit bb1f20f053fe20ef736461b9b7ad544bd2eea8ab.
2026-05-01 Replaced `CONTROLLER_ENABLE` with `CONTROLLER_MOTOR_ENABLE` where the motor control themselves can be switched.
2026-05-01 Fixed bug in `VideoMaker` when the first image frame is corrupted and the initialization `cv2.VideoWriter` is attempted anyways.
2026-05-01 Marking `MainFlightComputer` target as flight-ready.
2026-05-01 Tweaked stepper motor driver settings for better performance.
2026-05-02 Expanded more on Remove-Before-Flight Procedure.
2026-05-02 Removed `DemoGNC` target and `plot` verb.
2026-05-03 Beginning to write technical documentation.
2026-05-05 Cleared some stale to-dos.
2026-05-05 Marked `DebugBoard` as flight-ready.
2026-05-05 Something with GNC.
2026-05-05 Added more details to Wallops Testing Procedure concerning vibration testing.
2026-05-09 Reimplemented algorithm...
2026-05-09 Corrected the rate damping duration.
2026-05-10 Fixed minor bug with `compressed_file_path` in `parseVideo`.
2026-05-11 Added scope braces for `sus`.
2026-05-13 Fixed division by zero.
2026-05-15 Added burnwire line images
2026-05-15 Cleaned up burn-wire assembly documentation.
2026-05-19 Revert "Some details about the build system."
    This reverts commit 81b4593b09b10742b82304b2ea2c7a55a2372b51.
2026-05-19 Expanded High-Level System Overview section.
